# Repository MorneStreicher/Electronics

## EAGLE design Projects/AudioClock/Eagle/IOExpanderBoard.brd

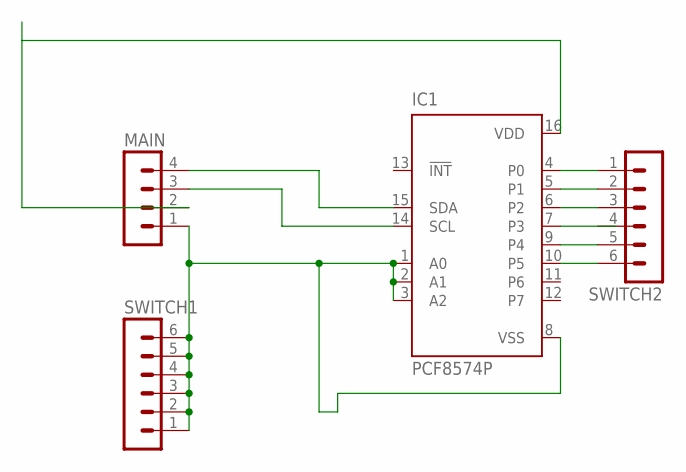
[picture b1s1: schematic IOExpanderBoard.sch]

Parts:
IC1: PCF8574P; DIL16
MAIN: MA04-1
SWITCH1, SWITCH2: MA06-1

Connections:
unnamed: IC1.9 (P4), SWITCH2.5
unnamed: IC1.16 (VDD), MAIN.2
unnamed: IC1.14 (SCL), MAIN.3
unnamed: IC1.15 (SDA), MAIN.4
unnamed: IC1.1 (A0), IC1.2 (A1), IC1.3 (A2), IC1.8 (VSS), MAIN.1, SWITCH1.1, SWITCH1.2, SWITCH1.3, SWITCH1.4, SWITCH1.5, SWITCH1.6
unnamed: IC1.4 (P0), SWITCH2.1
unnamed: IC1.5 (P1), SWITCH2.2
unnamed: IC1.6 (P2), SWITCH2.3
unnamed: IC1.10 (P5), SWITCH2.6

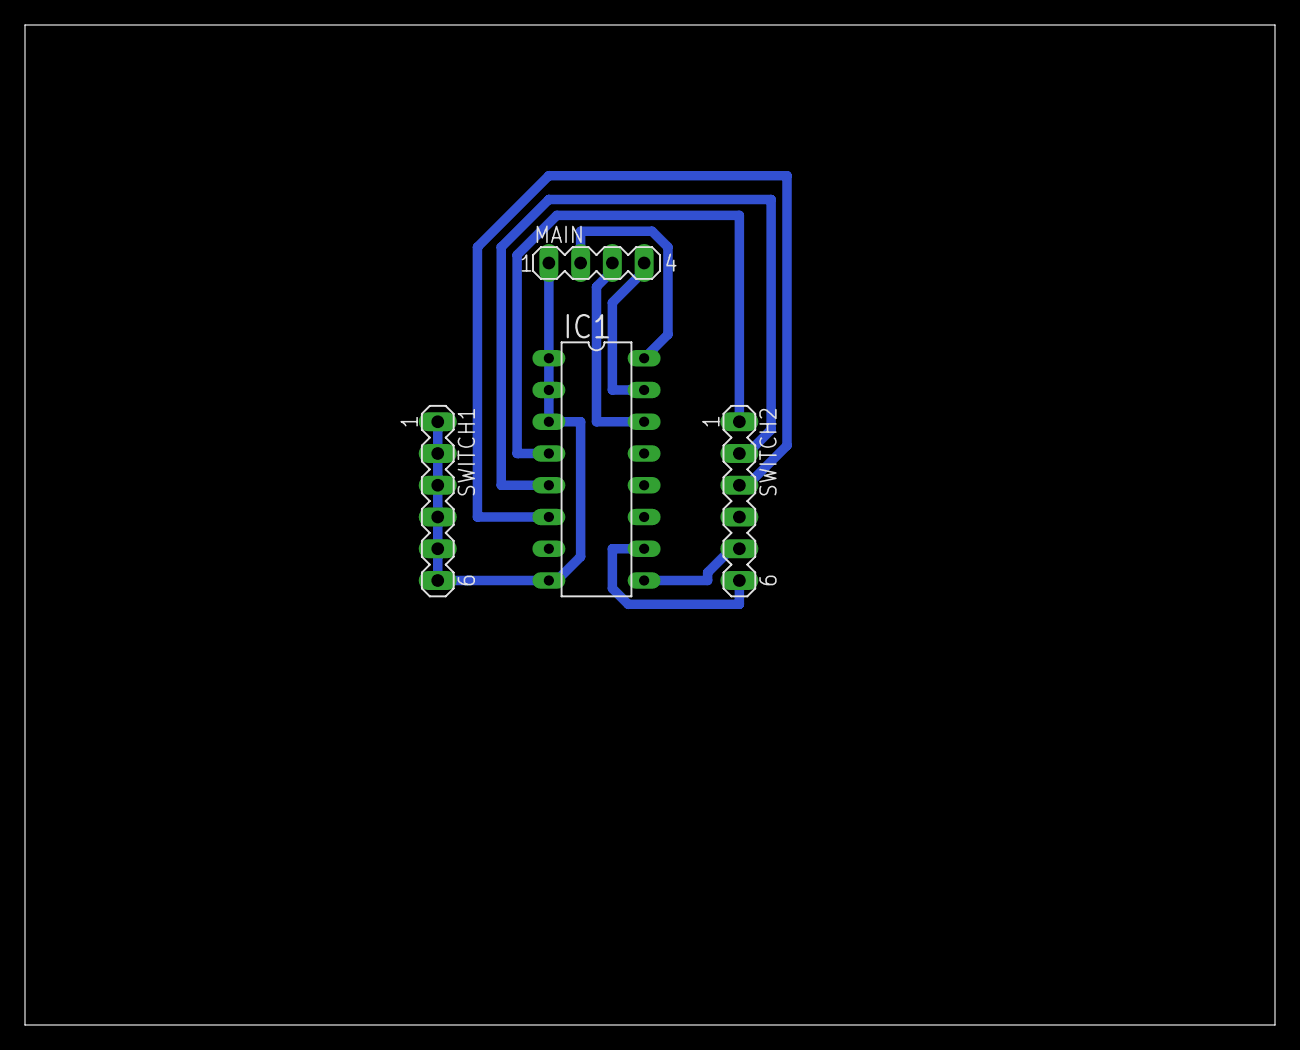
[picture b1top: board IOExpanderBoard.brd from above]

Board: 2 copper layers, 100.0 x 80.0 mm, 4 parts (0 on the bottom side), 9 nets.

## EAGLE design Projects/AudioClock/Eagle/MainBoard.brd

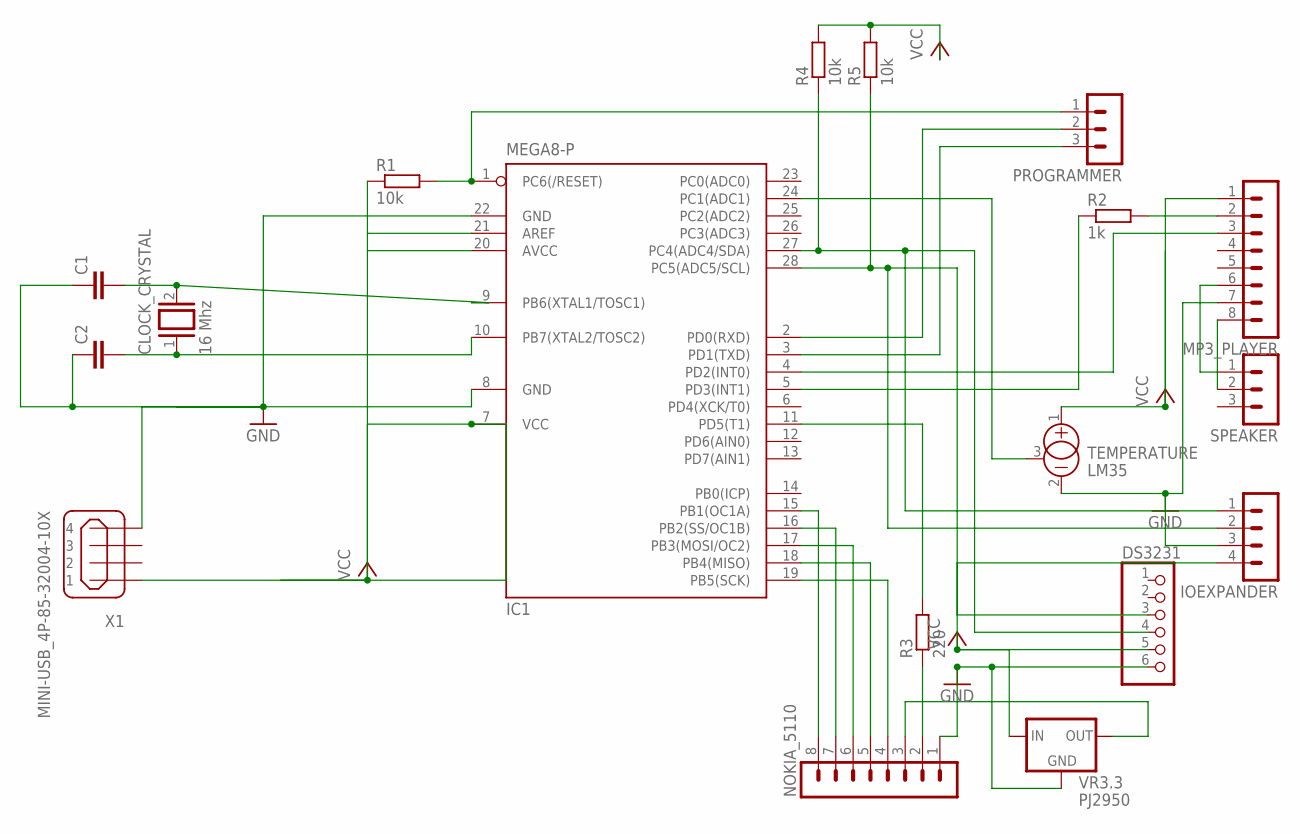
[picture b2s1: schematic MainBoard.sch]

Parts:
C1, C2: C2,5-3; C2.5-3
CLOCK_CRYSTAL: 16 Mhz; QS
DS3231: PINHD-1X6; 1X06
IC1: MEGA8-P; DIL28-3
IOEXPANDER: MA04-1
MP3_PLAYER: MA08-1W
NOKIA_5110: MA08-1
PROGRAMMER: MA03-1
R1, R4, R5: 10k; 0204/7
R2: 1k; 0204/7
R3: 220; 0204/7
SPEAKER: MA03-1
TEMPERATURE: LM35; TO92
VR3.3: PJ2950; 78LXX
X1: MINI-USB_4P-85-32004-10X; 85-32004-10X

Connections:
GND: C1.1, C2.1, DS3231.6, IC1.8 (GND), IC1.22 (GND), IOEXPANDER.3, MP3_PLAYER.7, NOKIA_5110.1, TEMPERATURE.2 (-), VR3.3.GND, X1.4
unnamed: DS3231.4, IC1.27 (PC4(ADC4/SDA)), IOEXPANDER.1, R4.1
unnamed: DS3231.3, IC1.28 (PC5(ADC5/SCL)), IOEXPANDER.2, R5.1
unnamed: IC1.24 (PC1(ADC1)), TEMPERATURE.3 (CAN)
unnamed: C1.2, CLOCK_CRYSTAL.2, IC1.9 (PB6(XTAL1/TOSC1))
unnamed: C2.2, CLOCK_CRYSTAL.1, IC1.10 (PB7(XTAL2/TOSC2))
unnamed: IC1.4 (PD2(INT0)), MP3_PLAYER.3
unnamed: IC1.1 (PC6(/RESET)), PROGRAMMER.1, R1.2
unnamed: IC1.2 (PD0(RXD)), PROGRAMMER.2
unnamed: IC1.3 (PD1(TXD)), PROGRAMMER.3
unnamed: MP3_PLAYER.2, R2.2
unnamed: IC1.5 (PD3(INT1)), R2.1
unnamed: IC1.15 (PB1(OC1A)), NOKIA_5110.8
unnamed: MP3_PLAYER.6, SPEAKER.1
unnamed: MP3_PLAYER.8, SPEAKER.2
unnamed: IC1.16 (PB2(SS/OC1B)), NOKIA_5110.7
unnamed: IC1.17 (PB3(MOSI/OC2)), NOKIA_5110.6
unnamed: IC1.18 (PB4(MISO)), NOKIA_5110.5
unnamed: IC1.19 (PB5(SCK)), NOKIA_5110.4
unnamed: NOKIA_5110.3, VR3.3.OUT
unnamed: NOKIA_5110.2, R3.1
unnamed: IC1.11 (PD5(T1)), R3.2
VCC: DS3231.5, IC1.7 (VCC), IC1.20 (AVCC), IC1.21 (AREF), IOEXPANDER.4, MP3_PLAYER.1, R1.1, R4.2, R5.2, TEMPERATURE.1 (+), VR3.3.IN, X1.1

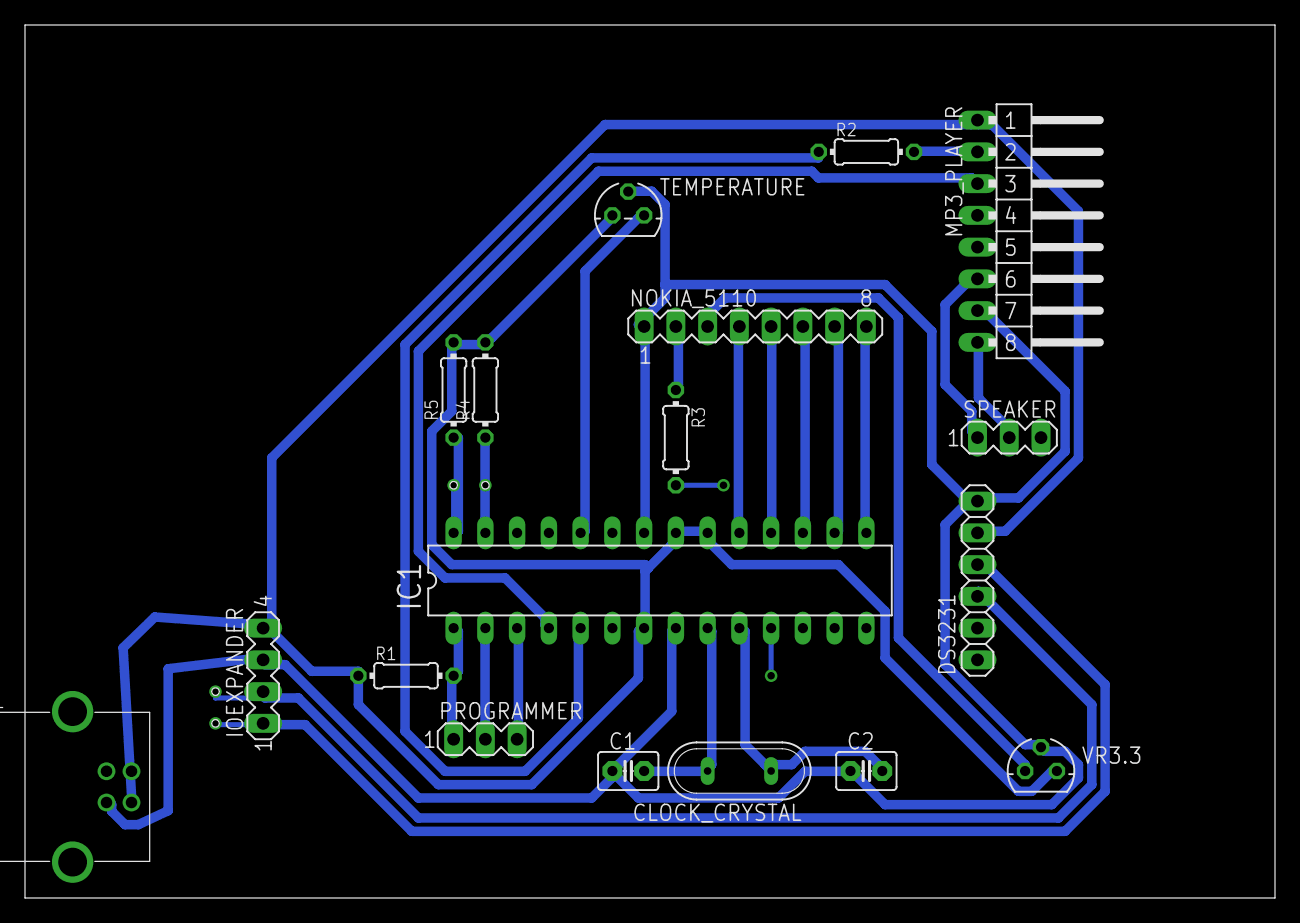
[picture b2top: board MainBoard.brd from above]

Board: 2 copper layers, 100.0 x 69.8 mm, 18 parts (0 on the bottom side), 23 nets.

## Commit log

2017-08-07 Added a few electronics projects.
2018-01-30 Initial commit of AudioClock
2018-04-08 Minor updates.
2020-07-10 FPGA Documents
